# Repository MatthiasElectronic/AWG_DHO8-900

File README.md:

Artificial Waveform Generator for DHO800 and DHO900 series
===

This is a daughter board for the Rigol DHO800 or DHO900 series oscilloscopes to add the missing hardware for the function generator.  
State: finished and working

[Download all files as zip archive here](https://github.com/MatthiasElectronic/AWG_DHO8-900/archive/refs/heads/main.zip)

Discussion thread: https://www.eevblog.com/forum/testgear/awg-function-generator-for-dho800-900-series-oscilloscopes/

Hands-On video by Thomas from "hochohmig": https://www.youtube.com/watch?v=W03NUFdP6oc

Table of Contents
===
1. [Target of this project](#target-of-this-project)
2. [Versions](#versions)
3. [Performance](#performance)
4. [Requirements](#requirements)
5. [Cost and Ordering](#cost-and-ordering)
6. [Interface between Mainboard and AWG daughter board](#interface-between-mainboard-and-awg-daughter-board)
7. [Topology discussion and design decisions](#topology-discussion-and-design-decisions)
8. [Possible Improvements](#possible-improvements)
9. [Thanksgiving](#thanksgiving)
10. [Disclaimer](#disclaimer)

Target of this project
-------
1. This is NOT a copy of the original function generator, but it uses the same interface and same DAC.
2. This design is optimized for cheap production including assembly, by the minimizing the amount of "extended components" from the JLCPCB manufacturer.
3. Minimizing distortion (THD) and noise (SNR) is achieved.
4. The ADC output filter is designed for better pulse and step response, therby having worse anti-alias attenuation (for >10MHz signals) and slight passband signal attenuation
5. Gain and offset tolerances are worse. A significant contributor is anyhow on the oscilloscope mainboard, so perfection cannot be achieved. However, if unlucky, tolerances in this project can mathematically hit quite hard.
6. As the original AWG, this function generator is designed for a 50 OHm coax cable with high impedance termination.

Versions
-------
V1: Original version, not recommended due to an offset bug and smaller mechanical misalignments.  
V2: Second version, not recommended due to a bug with OPA2673 sometimes getting hot. The fix with V3 is to connected Pins A0 and A1 to GND instead of -6.5V.  
V3: Recommended version.  
More details are in the history page in the schematic.

Performance
---
All signals are created with this AWG board, mounted on a DHO804 with a DHO924S vendor.bin.  
Measured on V1 PCB with the modifications of the V2 schematic.  

### Switching edges of a rectangular waveform
The switching edges are clean. trise & tfall are 15.5ns. This is a picture of maximum amplitude (+/-5V), but rise and fall times were measured identical for smaller voltages.  

### Bandwidth
The -3dB point is slightly above 25MHz. At the maximum selectable frequency of 25MHz, a peak-to-peak voltage of 719mV is measured, which is just above the 707mV of the -3dB point.  

### Distortion / THD
Distortion is over the most parts independent from the amplitude, just at very small amplitudes this is different.  
Here, a measurement of a 1kHz sine signal at 10V and 100mV peak-to-peak voltage is provided.  
At 10Vpp, the dominant HD3 is at ca. -62dB, so THD should be below -60dB.  

### Noise / SNR
**Noise measurement setup:**  
A sine signal at very low frequency is applied, the trigger is set to the crossover and the horizontal range is small such that the signal appears as DC.  
→ This way, AC RMS can be measured and equals the RMS noise at that signal amplitude. However, ultra low frequency noise is not visible.

**Noise at 2Vpp signal amplitude:**  
  
Noise RMS = 334µV, Signal RMS = 707mV => SNR = 67dB

**Noise at 10Vpp signal amplitude:**  
  
Noise RMS = 5.2mV, Signal RMS = 3.54V => SNR = 57dB

**Noise source**  
The measured noise levels are dominated by ripples/spikes from radiated EMI of the switching requlators on the mainboard with unshielded inductors.  
A 1.3MHz ripple is always present.  
A 740kHz ripple is only visible for >2Vpp, when the x10 gain stage (relay K4) is active..  
In the following FFT of a 10Vpp 1MHz sine signal, both ripples appear as peaks:  
  
Luckily, this is coupled into the circuit before the attenuators, so at smaller signal amplitudes also the EMI ripple is attenuated.

In addition, there are random (burst mode) spikes clearling coming from the PSU brick. They can even be measured with the AWG switched off.  

**To clarify: The noise/ripple is small enough, it is not visible in time domain unless having a very small amplitude.**

### Gain and Offset accuracy
My prototype has -3mV DC offset, coming directly from the motherboard on the target "DC offset" pin. This is the most noticable offset error, because this one is fully visible at the smallest signal amplitudes.  
Fixed this for my board, but this is completely related to tolerance. Additional offset errors are given in dependency of the AC gain and range selection, also this is amplified by 10 when the output signal exceeds 1Vp.  

My oscilloscope mainboard has a gain error of 3% between highest and lowest gain reference value. This is the most dominant part of the gain error, so if there is a need to fix this tolerance, this has to be done specific for each oscilloscope.

Requirements
--------
**Change vendor.bin**  
To add this AWG to the oscilloscope, a modified vendor.bin (DHO914S or DHO924S) to enable the AWG software functionalities is required.
https://www.eevblog.com/forum/testgear/hacking-the-rigol-dho800900-scope/msg5344076/#msg5344076

**Offset Removal**  
After modifying the vendor.bin, a DC offset in the analog measurement channels is there and might even not be removable by recalibration.  
A firmware update AFTER changing the vendor.bin, followed by a recalibration helps. I assume that the FPGA fimware is changed during a firmware update in dependency of the vendor.bin.

**Hardware version resistors**  
Update: There is no need to change the resistors for version detection - both DHO800 and DHO900 series oscilloscopes work without changing resistors.

**Add missing components to the mainboard**  
The DHO800 series oscilloscopes are missing some parts on the mainboard.  
- The connectors (1.27mm female sockets) 2x20 and 2x5 have to be added (this might be helpful, thanks to Mechatrommer: https://www.youtube.com/watch?v=dBg6KQtSWTM)
- Two OP Amps (3PEAK TP1282L1-VR) have to be added for the offset and gain analog values. These are not really suited for this operation (because they are not officially input rail-rail), but somehow this still works and they are also placed on the original DHO900 series.
- The BNC connector is missing, but as this part is extremely high and nowhere to find, I instead increased the AWG PCB size and simply mounted a smaller BNC connector on the AWG board. So no extra BNC connector on the mainboard. When soldering the BNC connector onto the daughterboard, I suggest to do this as the last step. The SMD PCB interconnects have some tolerance and also the BNC connector ideally should not be pushed completely into the PCB to achieve the same height as the "trigger out" from the mainboard. I aligned the connector before soldering with the AWG daughterboard mounted on the mainboard.
- The board needs to be fixed to the mounting holes. M4 screws with two M4 fasteners were sufficient, but are slightly too large (soldermask IS the isolation...). A better solution (idea from hochohmig.de) are solderable M3 through hole taps, this is cleaner and does not require access to the backside of the mainboard. Securing the daughterboard to the mainboard with the mounting holes is absolutely necessary, the PCB interconnects alone are not sufficient as the BNC connector is not fastened to the case.
- A hole needs to be drilled in the plastic casing for the BNC connector.  

Luckily, all remaining components (resistors, reference voltages, digital interface, …) are already assembled.

**It is NOT necessary to add any additional RAM to the DHO800 series.**

Cost and Ordering
-------
Total cost for 1 board should be ca. 50€.

All components (apart from the connectors) are soldered on the top layer. The PCB is a four layer board.  
This allowed economic assembly with JLCPCB (not sponsored), which is very cheap when using the preferred components. So the whole design is optimized around these preferred components to keep cost low. However, there are some components that are extended (and this costs ca. 3€ each extra). So most of them were ordered on LCSC, because this order was anyways necessary for the connectors and the OP-Amps on the main board.
All parts in this design files have a LCSC number, which makes ordering at LCSC or JLCPCB very simple.
Just be sure that you
1. Have a hot air station or let the QFN packages be soldered (DAC & OP-Amp). Even when ignoring the bottom central GND-pad, this won’t be easy with a simple soldering iron.
2. Use a four layer bord with the recommended or a similar stackup as documented on the first page of the schematic to have somewhat correct impedances.
3. Have accessable vias such that you can use them as measurement points if something does not work.
4. Do not choose a different inductor with a larger height for the step down converters, as there is no space to the casing.

When keeping extended components low (I only chose the SMD inductor), then this can be quite cheap. I ended up with 34€ on JLCPCB for 5 partly assembled boards and 41€ on LCSC for components for 2 boards, including tax and shipment. This adds up to 75€. It should be ca. 53€ if I only ordered components for 1 board. (05/2025)

Interface between Mainboard and AWG daughter board
----
CLK = Sample rate = 156MHz  
The digital data is ALWAYS completely using up the headroom of the DAC.  
Adjustments on the gain are only done by the analog gain input voltage, not digitally.  
With Amplitude = Vpp set to 2V, all attenuation/amplification stages K1-K4 are disabled and the analog gain input is at its maximum value.  
Still unclear is the "Protection" output signal, also it seems strange that this has to be pulled down to negative voltage.  
The 5 relays are: /sqrt(10), /10, /10, *10, On/Off

Topology discussion and design decisions
---
The topolology is  

The DAC itself is the same as on the original AWG board, but in a much cheaper QFN package. The allowed DAC output current was significantly overdriven in the original design, thus I reduced this current.

The OP amps are completely exchanged in favor for the price. The original 1GHz part just seemed to be overkill for a 50MHz signal generator. I chose the 230MHz OPA2673 instead. Sadly, there is nothing cheap in between that has high voltage and high bandwith. But the slew rate is sufficient.

Power rails are reduced to only +6.5V and -6.5V, which is just sufficient for the maximum +5V / -5V signal output voltage and at the border of the allowed OP amp operating conditions. These are both switchers, ripple is kept low by having forced PWM and filtering directly at the OP amp inputs. There is no need for LDOs as most LDOs cannot remove the 1.1MHz ripple. The 5V relays are rated for this voltage, so this is great as well.
Although the original board had +15V/-12V, the same maximum output signal is achieved. Having only 6.5V means that the DC offset stage had to be redone, therefore all PI attenuators and OP amp gains had to be changed. As an easy addon, I also added matched impedances on the PCB.

The DAC output filter is completly redone. The original filter required very specific and uncommon component values, which are nowhere availlable, so this had to be completely changed.

In the original design there was a 9th oder elliptic filter, which sounds great for HF suppression, but has a terrible step response. As I wanted solid edges for rectangular signals, I opted for a filter with a much better phase. While also optimizing for minimum component variation, this turned out to be a bit „creative“ and a 5th order lowpass filter (somewhere in between butterworth and bessel). Simulation in Spice looked promising, but the measured edges (see above, trise/fall = 15.5ns) are slightly slower than simulated (10ns).

As can be seen below, the step response is much better while not exceeding the OP ampl slew rate. Looking at the attenuation over frequency, obviously the elliptic filter is better. My filter has a slight attenuation in the upper passband and a not so perfect attenuation at the sample frequency (156MHz).

Attenuation in the passband: This is noticable for frequencies above 10MHz, but can be corrected for sine signals by manually adjusting the amplitude.

Aliasing: Aliasing can only occur above the Nyquist frequency (78MHz). For signals with lower frequencies (e. g. <1MHz), where fsig << fsample, this is not important as the sinc-behavior in the frequency domain of the sample and hold circuit does sufficently suppress any aliasing (sinc(1-1MHz/156MHz)=-44dB), in addition to the lowpass attenuation. For larger frequencies, this will be worse and probably noticable in the FFT or a spectrum viewer.

Conclusion:  
→ a worse aliasing attenuation, relevant only at high frequencies
→ a better behavior in the step and impulse response

Possible Improvements
---
...which I am not going to solve, but feel free to contribute.  
- the M4 fasteners are too large, more space is required as the solder mask is currently the only line of defence.  
- a DC offset potentiometer would be helpful  
- improve the gain accuracy, but this can get very difficult  
- choose connectors with through-hole alignment pins for easier assembly, but this might require better measurement of the dimensions.
- Eliminate the magnetic EMI incoupling of the switching regulators on the mainboard. Easiest solution could be swapping layer 3 (GND) and layer 4 (signal) and correcting trace widths for the impedances.
  However, as this is magnetic near field, this might not be sufficent. I tried some aluminum kitchen foil connected to GND as a shield, which brought -3dB. A floating thin iron sheet brought -10dB.
  Another option could be to replace the unshielded inductors on the main board with shielded ones.

Be warned that on the left hand side from the relays, the plastic case gets very close to the PCB, so even large MLCCs or SMD inductors can be too large and the relays definitly are.

Thanksgiving
---
Thanks to  
Everybody contributing to the [Hacking the Rigol DHO800/900 Scope](https://www.eevblog.com/forum/testgear/hacking-the-rigol-dho800900-scope/) thread  
Pu6k1n [EEVBlog] for the [schematic of the reverse-engineered original AWG](https://www.eevblog.com/forum/testgear/hacking-the-rigol-dho800900-scope/?action=dlattach;attach=2492911), the pinning helped a lot  
AndyBig [EEVBlog] for all information about DHO800 to DHO900 vendor.bin modification and reporting a bug with V2  
Mechatrommer [EEVBlog] for inspiration from his own AWG attempt and lots of tiny information  
Thomas from [hochohmig.de](https://www.hochohmig.de/) for providing calculation tools, testing the board and creating a [demonstration video - check out his channel](https://www.youtube.com/watch?v=W03NUFdP6oc&t=1s)  
Contributers to KiCad and the library plugins

Disclaimer
---
This is published with CERN-OHL-W-2.0 license, which is accessible in license.txt.
No liability is provided for this not working or causing any form of damage or harm. This is not a product, but a development board. Use at your own risk.  
This project is influenced by the original AWG from Rigol, so only recommended for personal use. Although not checked, selling this AWG could possibly violate patents or rights of Rigol.

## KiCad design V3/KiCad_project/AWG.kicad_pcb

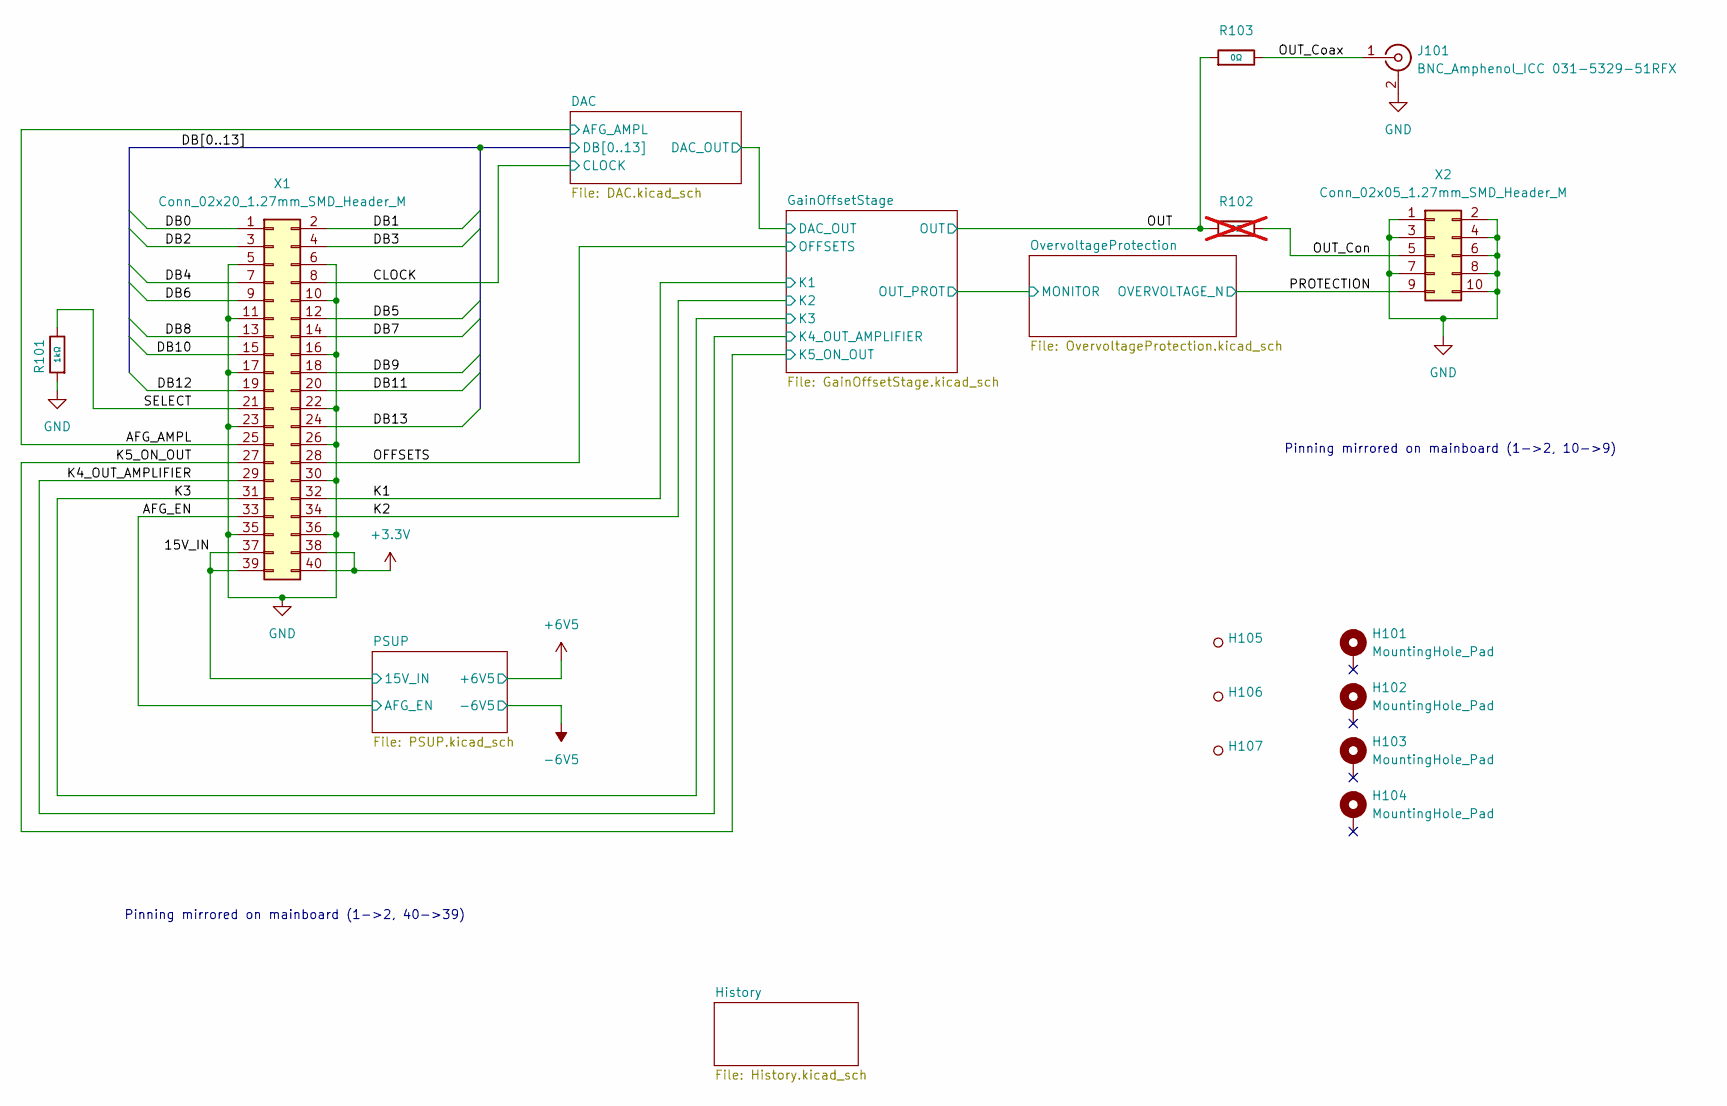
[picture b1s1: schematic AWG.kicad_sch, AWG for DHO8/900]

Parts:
H101, H102, H103, H104: MountingHole_Pad; MountingHole_4.0mm_SmallPad
H105, H106, H107: Hole_Tooling_JLCPCB
J101: BNC_Amphenol_ICC 031-5329-51RFX; LCSC C5443992
R101: 1kΩ; R_0603; Overload Voltage (Max) 75V; Tolerance ±1%; Part 0603WAF1001T5E; LCSC C21190
R102: 0Ω; R_0603; Overload Voltage (Max) 75V; Tolerance ±1%; Part 0603WAF0000T5E; LCSC C21189; not fitted
R103: 0Ω; R_0603; Overload Voltage (Max) 75V; Tolerance ±1%; Part 0603WAF0000T5E; LCSC C21189
X1: Conn_02x20_1.27mm_SMD_Header_M; PinHeader_2x20_P1.27mm_Vertical_SMD; LCSC C2881925
X2: Conn_02x05_1.27mm_SMD_Header_M; PinHeader_2x05_P1.27mm_Vertical_SMD; LCSC C2881910

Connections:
+3.3V: X1.38, X1.40; also elsewhere on the board
/15V_IN: X1.37, X1.39; also elsewhere on the board
/AFG_AMPL: X1.25; also elsewhere on the board
/AFG_EN: X1.33; also elsewhere on the board
/CLOCK: X1.8; also elsewhere on the board
/DB0: X1.1; also elsewhere on the board
/DB1: X1.2; also elsewhere on the board
/DB2: X1.3; also elsewhere on the board
/DB3: X1.4; also elsewhere on the board
/DB4: X1.7; also elsewhere on the board
/DB5: X1.12; also elsewhere on the board
/DB6: X1.9; also elsewhere on the board
/DB7: X1.14; also elsewhere on the board
/DB8: X1.13; also elsewhere on the board
/DB9: X1.18; also elsewhere on the board
/DB10: X1.15; also elsewhere on the board
/DB11: X1.20; also elsewhere on the board
/DB12: X1.19; also elsewhere on the board
/DB13: X1.24; also elsewhere on the board
/K1: X1.32; also elsewhere on the board
/K2: X1.34; also elsewhere on the board
/K3: X1.31; also elsewhere on the board
/K4_OUT_AMPLIFIER: X1.29; also elsewhere on the board
/K5_ON_OUT: X1.27; also elsewhere on the board
/OFFSETS: X1.28; also elsewhere on the board
/OUT: R102.1, R103.1; also elsewhere on the board
/OUT_Coax: J101.1 (In), R103.2
/OUT_Con: R102.2, X2.5
/PROTECTION: X2.9; also elsewhere on the board
/SELECT: R101.2, X1.21
GND: J101.2 (Ext), R101.1, X1.5, X1.6, X1.10, X1.11, X1.16, X1.17, X1.22, X1.23, X1.26, X1.30, X1.35, X1.36, X2.1, X2.2, X2.3, X2.4, X2.6, X2.7, X2.8, X2.10; also elsewhere on the board

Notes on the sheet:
Pinning mirrored on mainboard (1->2, 40->39)
Pinning mirrored on mainboard (1->2, 10->9)

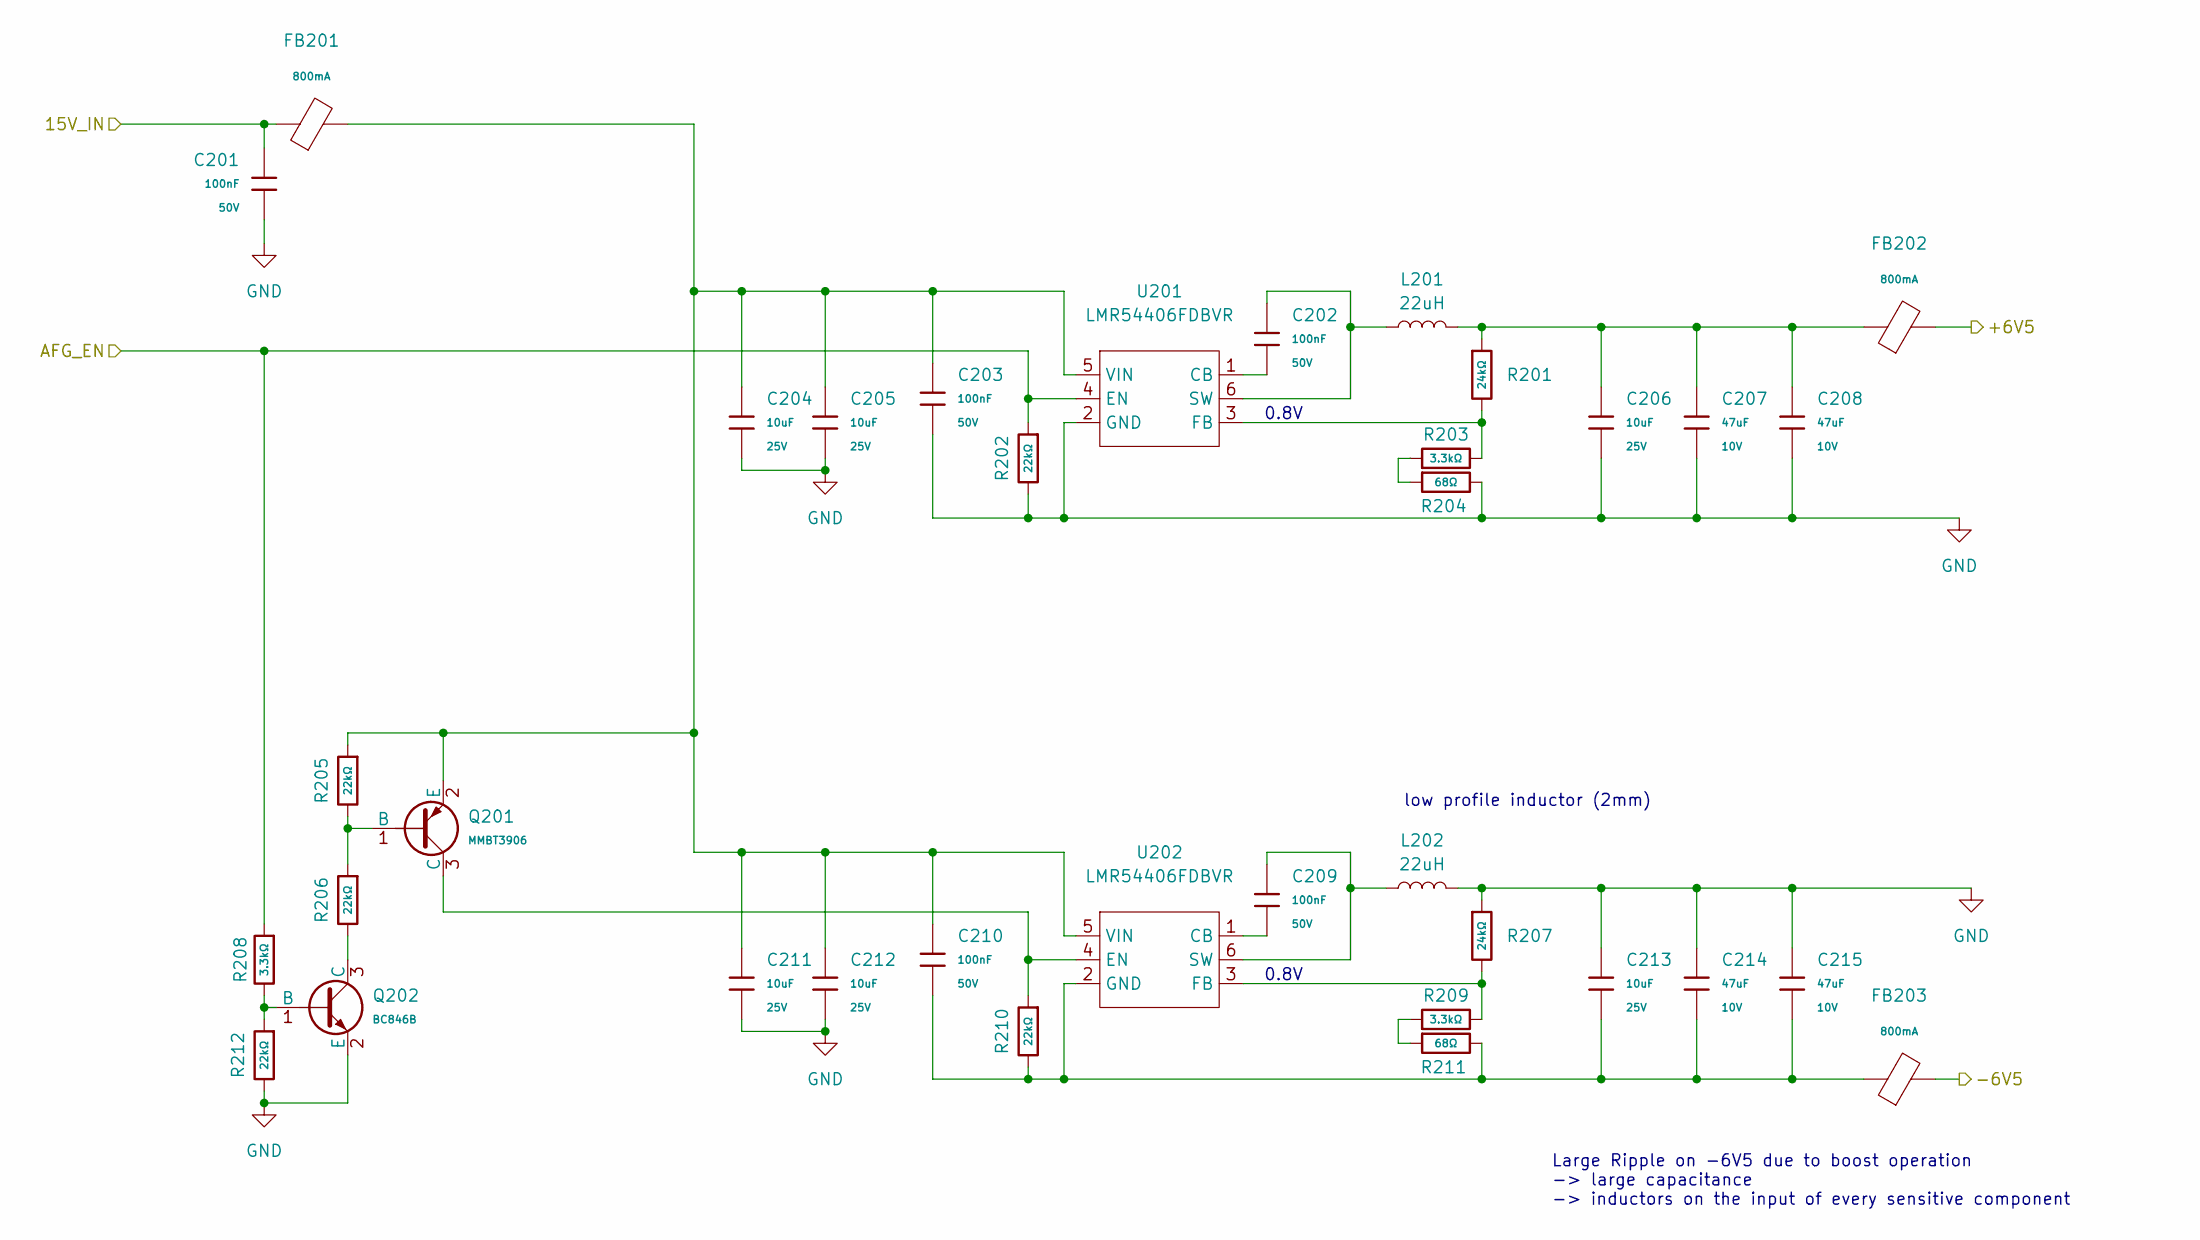
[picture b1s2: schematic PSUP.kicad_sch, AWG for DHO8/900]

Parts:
C201, C202, C203, C209, C210: 100nF; C_0603; Voltage Rated 50V; Tolerance ±10%; Part CC0603KRX7R9BB104; LCSC C14663
C204, C205, C206, C211, C212, C213: 10uF; C_0805; Voltage Rated 25V; Tolerance ±10%; Part CL21A106KAYNNNE; LCSC C15850
C207, C208, C214, C215: 47uF; C_1206; Voltage Rated 10V; Tolerance ±20%; Part CL31A476MPHNNNE; LCSC C96123
FB201, FB202, FB203: FB_0805; Current Rating 800mA; Tolerance ±25%; Part GZ2012D101TF; LCSC C1015
L201, L202: 22uH; L_APV_ANR5045; LCSC C440232
Q201: MMBT3906; Q_SOT-23; Part MMBT3906; LCSC C7420354
Q202: BC846B; Q_SOT-23; Part BC846B; LCSC C20069134
R201, R207: 24kΩ; R_0603; Overload Voltage (Max) 75V; Tolerance ±1%; Part 0603WAF2402T5E; LCSC C23352
R202, R205, R206, R210, R212: 22kΩ; R_0603; Overload Voltage (Max) 75V; Tolerance ±1%; Part 0603WAF2202T5E; LCSC C31850
R203, R208, R209: 3.3kΩ; R_0603; Overload Voltage (Max) 75V; Tolerance ±1%; Part 0603WAF3301T5E; LCSC C22978
R204, R211: 68Ω; R_0603; Overload Voltage (Max) 75V; Tolerance ±1%; Part 0603WAF680JT5E; LCSC C27592
U201, U202: LMR54406FDBVR; SOT-23-6; Manufacturer Part LMR54406FDBVR; LCSC C3193129

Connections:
+6V5: FB202.2; also elsewhere on the board
-6V5: FB203.2; also elsewhere on the board
/15V_IN: C201.1, FB201.1; also elsewhere on the board
/AFG_EN: R202.1, R208.1, U201.4 (EN); also elsewhere on the board
GND: C201.2, C203.2, C204.2, C205.2, C206.2, C207.2, C208.2, C211.2, C212.2, C213.1, C214.1, C215.1, L202.2, Q202.2 (E), R202.2, R204.2, R207.1, R212.2, U201.2 (GND); also elsewhere on the board
unnamed: C206.1, C207.1, C208.1, FB202.1, L201.2, R201.1
unnamed: Q201.1 (B), R205.2, R206.1
unnamed: Q201.3 (C), R210.1, U202.4 (EN)
unnamed: C203.1, C204.1, C205.1, C210.1, C211.1, C212.1, FB201.2, Q201.2 (E), R205.1, U201.5 (VIN), U202.5 (VIN)
unnamed: Q202.1 (B), R208.2, R212.1
unnamed: Q202.3 (C), R206.2
unnamed: R203.1, R204.1
unnamed: R209.1, R211.1
unnamed: C202.2, U201.1 (CB)
unnamed: R201.2, R203.2, U201.3 (FB)
unnamed: C202.1, L201.1, U201.6 (SW)
unnamed: C209.2, U202.1 (CB)
unnamed: R207.2, R209.2, U202.3 (FB)
unnamed: C210.2, C213.2, C214.2, C215.2, FB203.1, R210.2, R211.2, U202.2 (GND)
unnamed: C209.1, L202.1, U202.6 (SW)

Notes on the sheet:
0.8V
Large Ripple on -6V5 due to boost operation -> large capacitance -> inductors on the input of every sensitive component
low profile inductor (2mm)

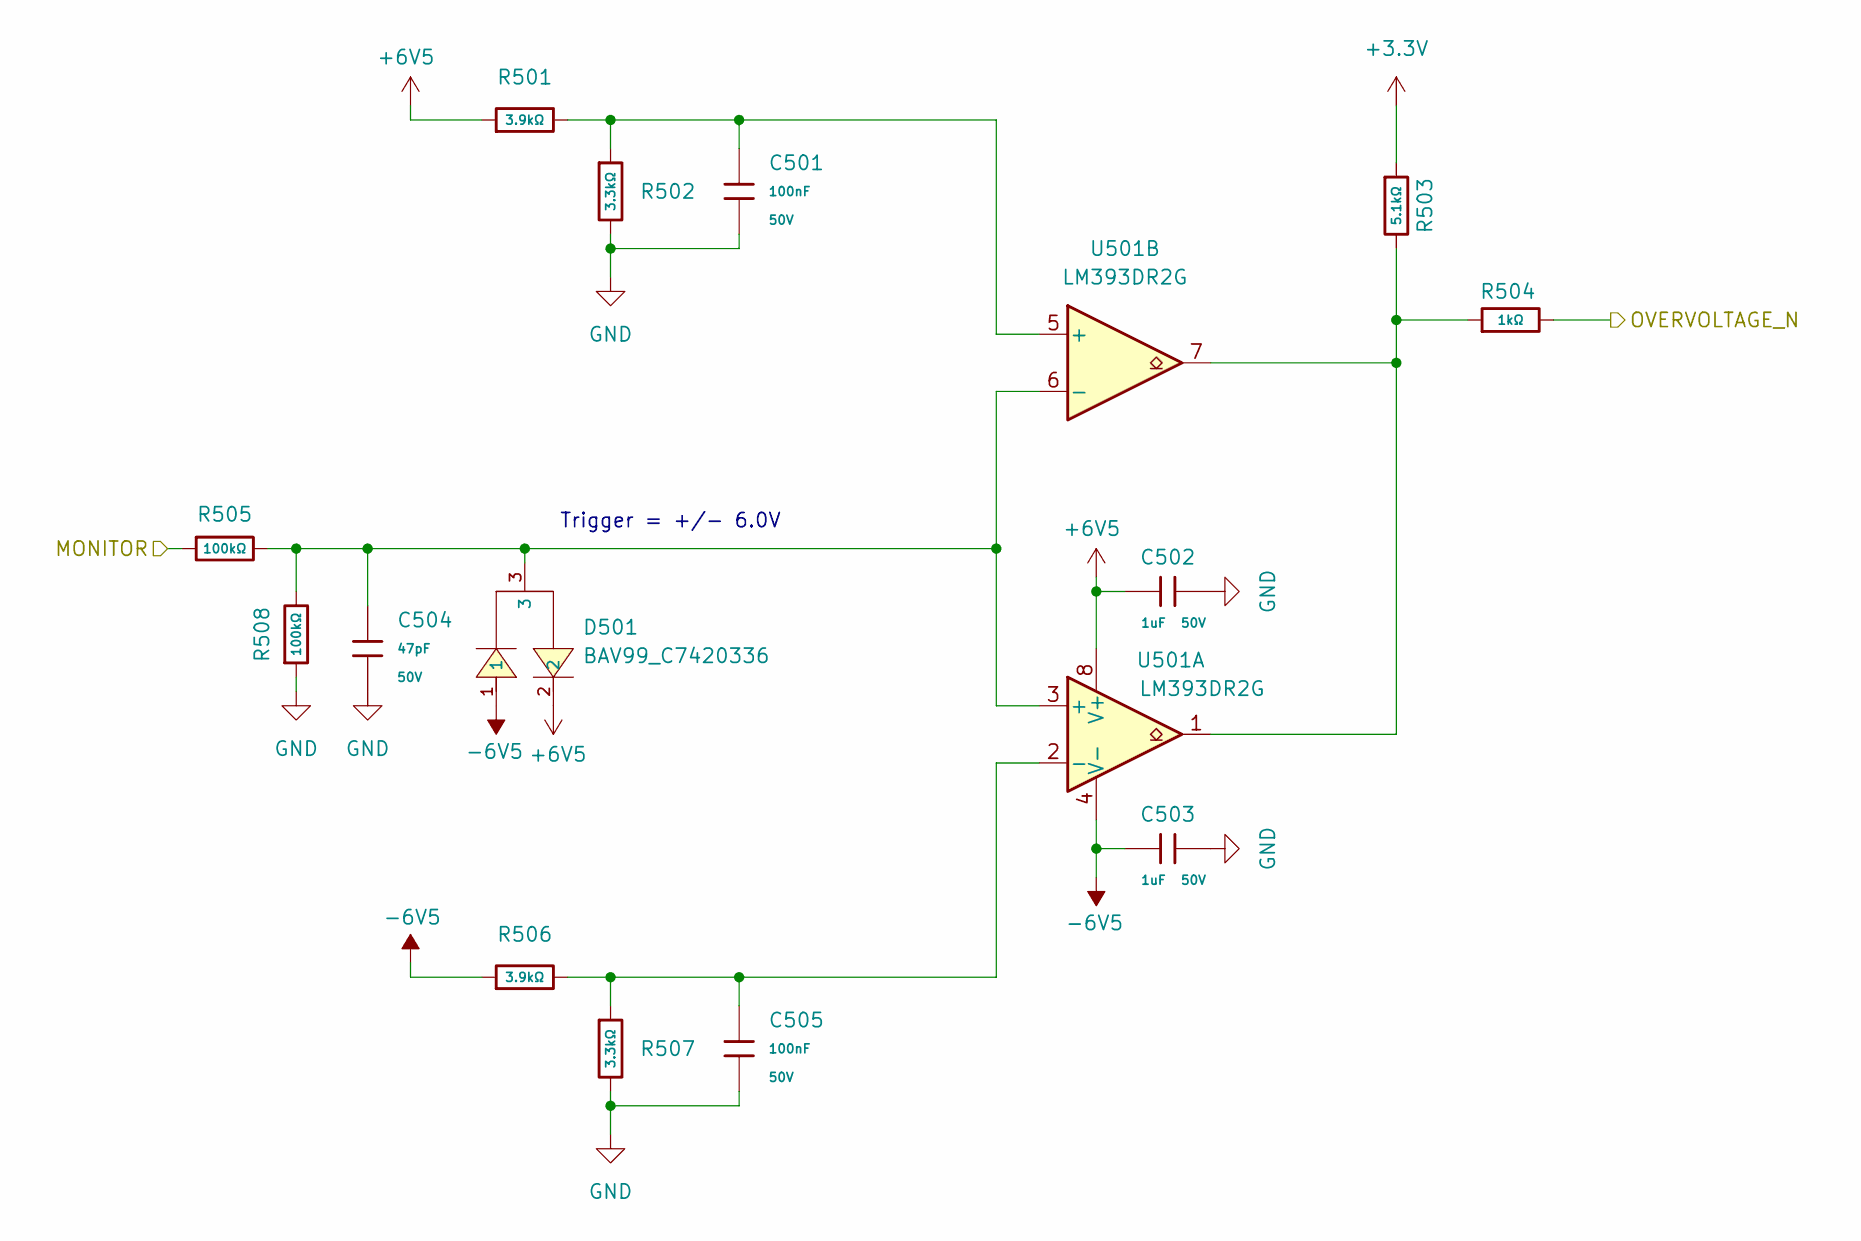
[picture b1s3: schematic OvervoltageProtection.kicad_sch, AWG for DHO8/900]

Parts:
C501, C505: 100nF; C_0603; Voltage Rated 50V; Tolerance ±10%; Part CC0603KRX7R9BB104; LCSC C14663
C502, C503: 1uF; C_0603; Voltage Rated 50V; Tolerance ±10%; Part CL10A105KB8NNNC; LCSC C15849
C504: 47pF; C_0603; Voltage Rated 50V; Tolerance ±5%; Part CL10C470JB8NNNC; LCSC C1671
D501: BAV99_C7420336; SOT-23-3_L2.9-W1.3-P1.90-LS2.4-BR; Reverse Voltage (Vr) 100V; Forward Voltage (Vf@If) 1.25V@150mA; Part BAV99; LCSC C7420336
R501, R506: 3.9kΩ; R_0603; Overload Voltage (Max) 75V; Tolerance ±1%; Part 0603WAF3901T5E; LCSC C23018
R502, R507: 3.3kΩ; R_0603; Overload Voltage (Max) 75V; Tolerance ±1%; Part 0603WAF3301T5E; LCSC C22978
R503: 5.1kΩ; R_0603; Overload Voltage (Max) 75V; Tolerance ±1%; Part 0603WAF5101T5E; LCSC C23186
R504: 1kΩ; R_0603; Overload Voltage (Max) 75V; Tolerance ±1%; Part 0603WAF1001T5E; LCSC C21190
R505, R508: 100kΩ; R_0603; Overload Voltage (Max) 75V; Tolerance ±1%; Part 0603WAF1003T5E; LCSC C25803
U501: LM393DR2G; SOIC-8_3.9x4.9mm_P1.27mm; LCSC C7955

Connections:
+3.3V: R503.1; also elsewhere on the board
+6V5: C502.1, D501.2, R501.1, U501.8 (V+); also elsewhere on the board
-6V5: C503.1, D501.1, R506.1, U501.4 (V-); also elsewhere on the board
/GainOffsetStage/OUT_PROT: R505.1; also elsewhere on the board
/PROTECTION: R504.2; also elsewhere on the board
GND: C501.2, C502.2, C503.2, C504.2, C505.2, R502.2, R507.2, R508.1; also elsewhere on the board
unnamed: R503.2, R504.1, U501.1, U501.7
unnamed: C504.1, D501.3, R505.2, R508.2, U501.3 (+), U501.6 (-)
unnamed: C505.1, R506.2, R507.1, U501.2 (-)
unnamed: C501.1, R501.2, R502.1, U501.5 (+)

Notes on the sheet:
Trigger = +/- 6.0V

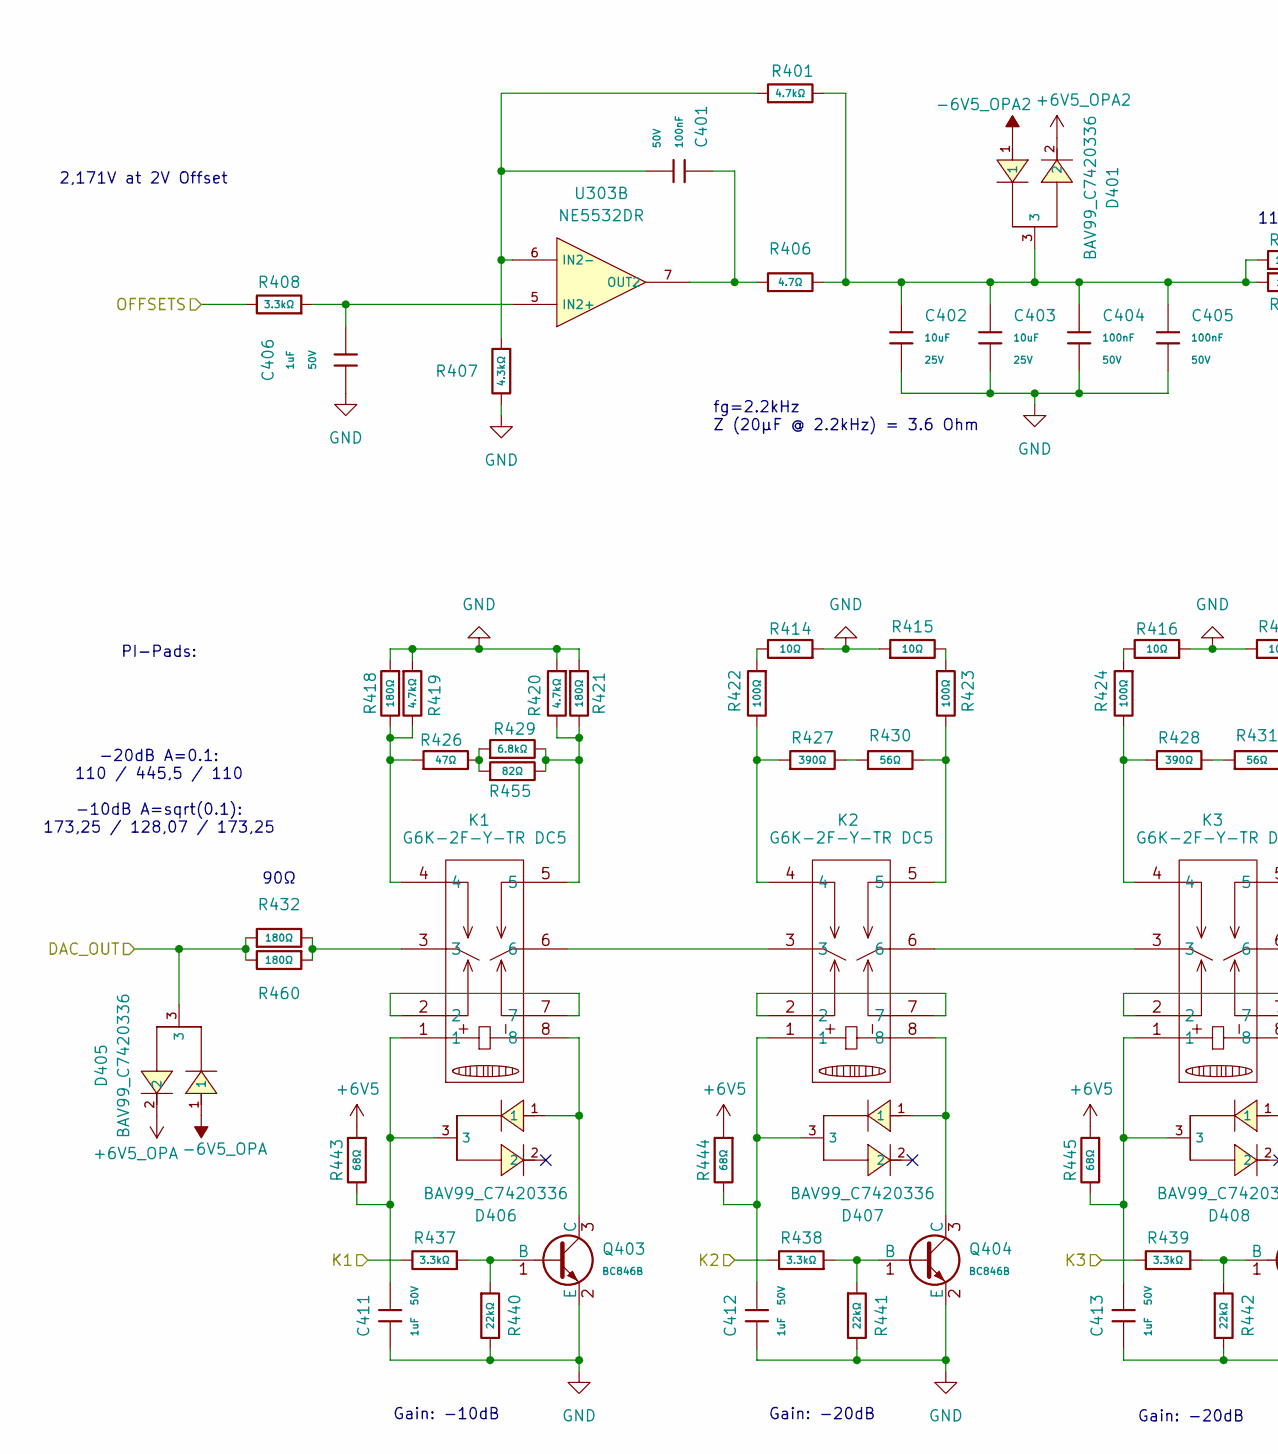
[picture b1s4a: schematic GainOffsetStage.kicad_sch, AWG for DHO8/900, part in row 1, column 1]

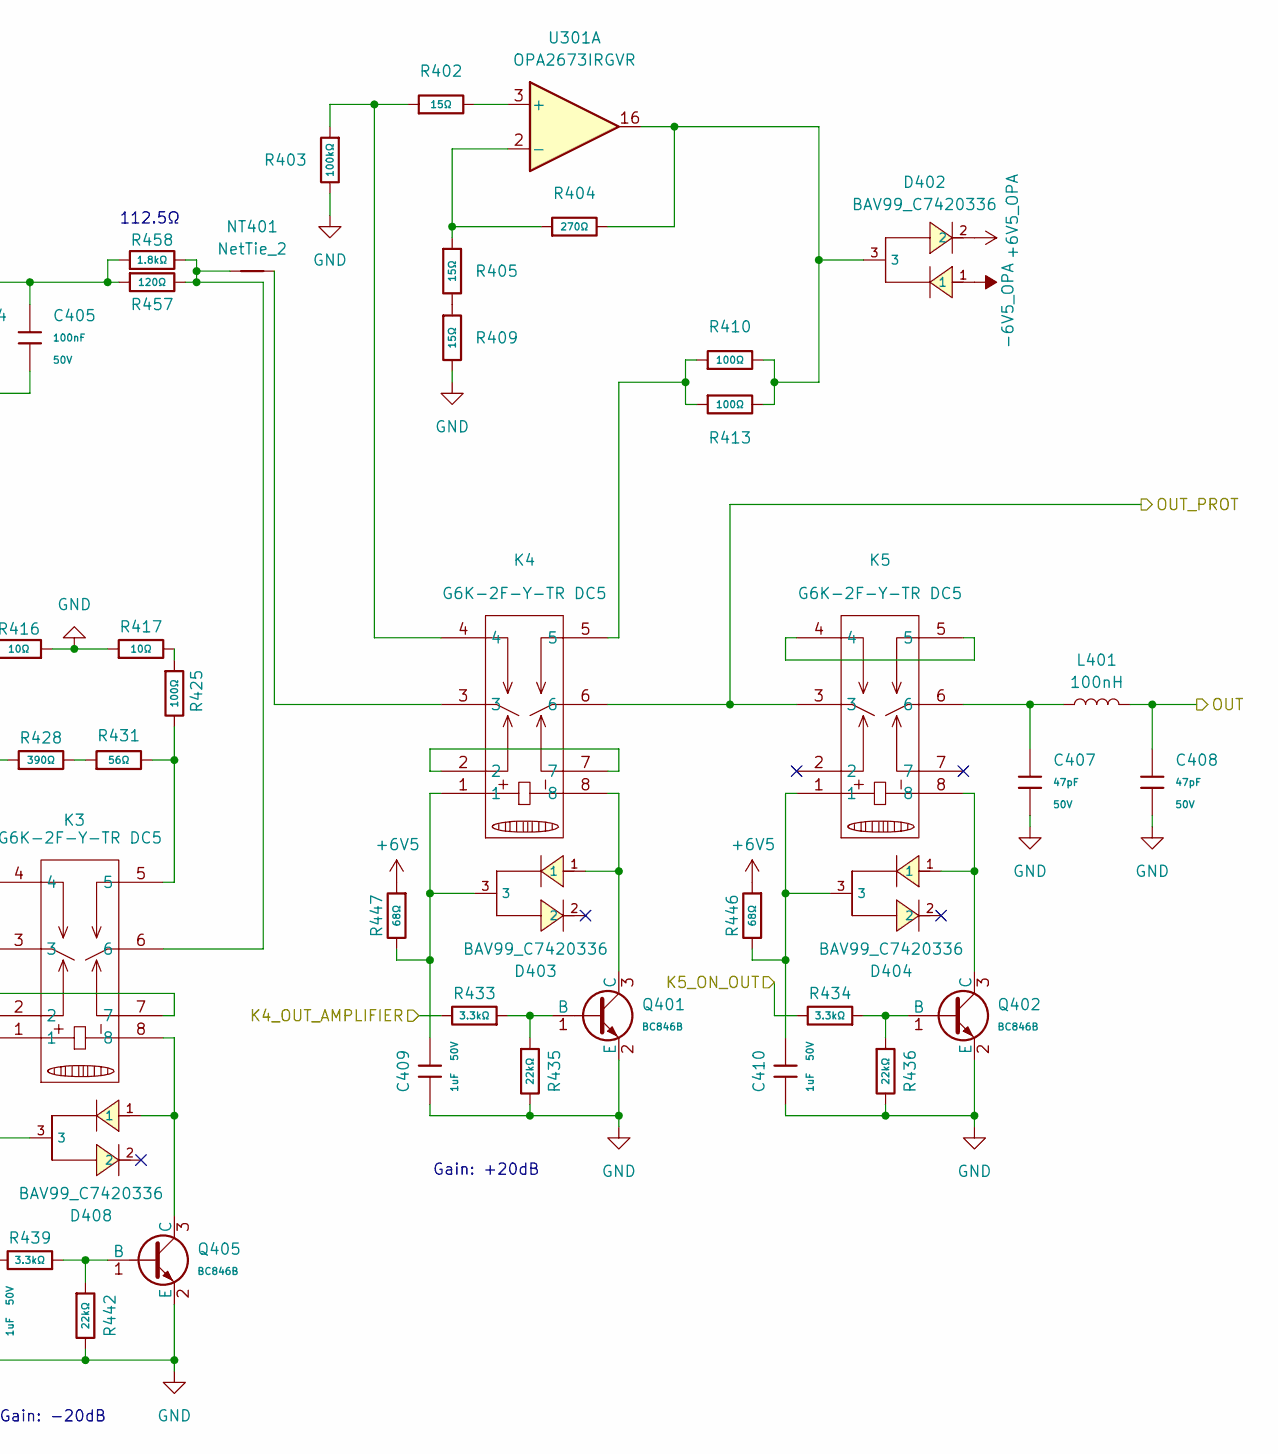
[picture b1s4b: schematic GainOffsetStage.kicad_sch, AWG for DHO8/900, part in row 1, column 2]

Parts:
C401, C404, C405: 100nF; C_0603; Voltage Rated 50V; Tolerance ±10%; Part CC0603KRX7R9BB104; LCSC C14663
C402, C403: 10uF; C_0805; Voltage Rated 25V; Tolerance ±10%; Part CL21A106KAYNNNE; LCSC C15850
C406, C409, C410, C411, C412, C413: 1uF; C_0603; Voltage Rated 50V; Tolerance ±10%; Part CL10A105KB8NNNC; LCSC C15849
C407, C408: 47pF; C_0603; Voltage Rated 50V; Tolerance ±5%; Part CL10C470JB8NNNC; LCSC C1671
D401, D402, D403, D404, D405, D406, D407, D408: BAV99_C7420336; SOT-23-3_L2.9-W1.3-P1.90-LS2.4-BR; Reverse Voltage (Vr) 100V; Forward Voltage (Vf@If) 1.25V@150mA; Part BAV99; LCSC C7420336
K1, K2, K3, K4, K5: RELAY-SMD_G6K-2F-X-XX; Manufacturer Part G6K-2F-Y-TR DC5; LCSC Part Name G6K-2F-Y-TR DC5
L401: 100nH; L_0603; LCSC C98088
NT401: NetTie_2; NetTie-2_SMD_Pad0.5mm
Q401, Q402, Q403, Q404, Q405: BC846B; Q_SOT-23; Part BC846B; LCSC C20069134
R401, R419, R420: 4.7kΩ; R_0603; Overload Voltage (Max) 75V; Tolerance ±1%; Part 0603WAF4701T5E; LCSC C23162
R402, R405, R409: 15Ω; R_0603; Overload Voltage (Max) 75V; Tolerance ±1%; Part 0603WAF150JT5E; LCSC C22810
R403: 100kΩ; R_0603; Overload Voltage (Max) 75V; Tolerance ±1%; Part 0603WAF1003T5E; LCSC C25803
R404: 270Ω; R_0805; Overload Voltage (Max) 150V; Tolerance ±1%; Part 0805W8F2700T5E; LCSC C17590
R406: 4.7Ω; R_0603; Overload Voltage (Max) 75V; Tolerance ±1%; Part 0603WAF470KT5E; LCSC C23164
R407: 4.3kΩ; R_0603; Overload Voltage (Max) 75V; Tolerance ±1%; Part 0603WAF4301T5E; LCSC C23159
R408, R433, R434, R437, R438, R439: 3.3kΩ; R_0603; Overload Voltage (Max) 75V; Tolerance ±1%; Part 0603WAF3301T5E; LCSC C22978
R410, R413: 100Ω; R_1206; Overload Voltage (Max) 200V; Tolerance ±1%; Part 1206W4F1000T5E; LCSC C17901
R414, R415, R416, R417: 10Ω; R_0603; Overload Voltage (Max) 75V; Tolerance ±1%; Part 0603WAF100JT5E; LCSC C22859
R418, R421, R432, R460: 180Ω; R_0603; Overload Voltage (Max) 75V; Tolerance ±1%; Part 0603WAF1800T5E; LCSC C22828
R422, R423, R424, R425: 100Ω; R_0603; Overload Voltage (Max) 75V; Tolerance ±1%; Part 0603WAF1000T5E; LCSC C22775
R426: 47Ω; R_0603; Overload Voltage (Max) 75V; Tolerance ±1%; Part 0603WAF470JT5E; LCSC C23182
R427, R428: 390Ω; R_0603; Overload Voltage (Max) 75V; Tolerance ±1%; Part 0603WAF3900T5E; LCSC C23151
R429: 6.8kΩ; R_0603; Overload Voltage (Max) 75V; Tolerance ±1%; Part 0603WAF6801T5E; LCSC C23212
R430, R431: 56Ω; R_0603; Overload Voltage (Max) 75V; Tolerance ±1%; Part 0603WAF560JT5E; LCSC C25196
R435, R436, R440, R441, R442: 22kΩ; R_0603; Overload Voltage (Max) 75V; Tolerance ±1%; Part 0603WAF2202T5E; LCSC C31850
R443, R444, R445, R446, R447: 68Ω; R_0603; Overload Voltage (Max) 75V; Tolerance ±1%; Part 0603WAF680JT5E; LCSC C27592
R455: 82Ω; R_0603; Overload Voltage (Max) 75V; Tolerance ±1%; Part 0603WAF820JT5E; LCSC C23255
R457: 120Ω; R_1206; Overload Voltage (Max) 200V; Tolerance ±1%; Part 1206W4F1200T5E; LCSC C17909
R458: 1.8kΩ; R_0603; Overload Voltage (Max) 75V; Tolerance ±1%; Part 0603WAF1801T5E; LCSC C4177
U301: OPA2673IRGVR; Texas_RSA_VQFN-16-1EP_4x4mm_P0.65mm_EP2.7x2.7mm; LCSC C1848168
U303: NE5532DR; SOIC-8_L4.9-W3.9-P1.27-LS6.0-BL; Part NE5532DR; LCSC C7426

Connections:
+6V5: R443.1, R444.1, R445.1, R446.1, R447.1; also elsewhere on the board
+6V5_OPA: D402.2, D405.2; also elsewhere on the board
+6V5_OPA2: D401.2; also elsewhere on the board
-6V5_OPA: D402.1, D405.1; also elsewhere on the board
-6V5_OPA2: D401.1; also elsewhere on the board
/DAC/DAC_OUT: D405.3, R432.1, R460.2; also elsewhere on the board
/GainOffsetStage/OUT_PROT: K4.6, K5.3; also elsewhere on the board
/K1: R437.2; also elsewhere on the board
/K2: R438.2; also elsewhere on the board
/K3: R439.2; also elsewhere on the board
/K4_OUT_AMPLIFIER: R433.2; also elsewhere on the board
/K5_ON_OUT: R434.2; also elsewhere on the board
/OFFSETS: R408.2; also elsewhere on the board
/OUT: C408.1, L401.2; also elsewhere on the board
GND: C402.2, C403.2, C404.2, C405.2, C406.1, C407.2, C408.2, C409.1, C410.1, C411.1, C412.1, C413.1, Q401.2 (E), Q402.2 (E), Q403.2 (E), Q404.2 (E), Q405.2 (E), R403.2, R407.2, R409.2, R414.1, R415.1, R416.1, R417.1, R418.1, R419.1, R420.1, R421.1, R435.2, R436.2, R440.2, R441.2, R442.2; also elsewhere on the board
unnamed: C402.1, C403.1, C404.1, C405.1, D401.3, R401.2, R406.2, R457.1, R458.1
unnamed: C407.1, K5.6, L401.1
unnamed: C409.2, D403.3, K4.1, R447.2
unnamed: C410.2, D404.3, K5.1, R446.2
unnamed: C411.2, D406.3, K1.1, R443.2
unnamed: C412.2, D407.3, K2.1, R444.2
unnamed: C413.2, D408.3, K3.1, R445.2
unnamed: D402.3, R404.2, R410.2, R413.2, U301.16
unnamed: K1.2, K1.7
unnamed: K1.3, R432.2, R460.1
unnamed: K1.4, R418.2, R419.2, R426.1
unnamed: K1.5, R420.2, R421.2, R429.2, R455.2
unnamed: K1.6, K2.3
unnamed: K2.2, K2.7
unnamed: K2.4, R422.2, R427.1
unnamed: K2.5, R423.2, R430.2
unnamed: K2.6, K3.3
unnamed: K3.2, K3.7
unnamed: K3.4, R424.2, R428.1
unnamed: K3.5, R425.2, R431.2
unnamed: K3.6, NT401.1, R457.2, R458.2
unnamed: K4.2, K4.7
unnamed: K4.3, NT401.2
unnamed: K4.4, R402.1, R403.1
unnamed: K4.5, R410.1, R413.1
unnamed: K5.4, K5.5
unnamed: Q401.1 (B), R433.1, R435.1
unnamed: D403.1, K4.8, Q401.3 (C)
unnamed: Q402.1 (B), R434.1, R436.1
unnamed: D404.1, K5.8, Q402.3 (C)
unnamed: Q403.1 (B), R437.1, R440.1
unnamed: D406.1, K1.8, Q403.3 (C)
unnamed: Q404.1 (B), R438.1, R441.1
unnamed: D407.1, K2.8, Q404.3 (C)
unnamed: Q405.1 (B), R439.1, R442.1
unnamed: D408.1, K3.8, Q405.3 (C)
unnamed: R405.2, R409.1
unnamed: R414.2, R422.1
unnamed: R415.2, R423.1
unnamed: R416.2, R424.1
unnamed: R417.2, R425.1
unnamed: R426.2, R429.1, R455.1
unnamed: R427.2, R430.1
unnamed: R428.2, R431.1
unnamed: R402.2, U301.3 (+)
unnamed: R404.1, R405.1, U301.2 (-)
unnamed: C406.2, R408.1, U303.5 (IN2+)
unnamed: C401.2, R401.1, R407.1, U303.6 (IN2-)
unnamed: C401.1, R406.1, U303.7 (OUT2)

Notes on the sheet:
PI-Pads:
Gain: +20dB
112.5Ω
Gain: -20dB
2,171V at 2V Offset
fg=2.2kHz Z (20µF @ 2.2kHz) = 3.6 Ohm
90Ω
Gain: -10dB
-20dB A=0.1: 110 / 445,5 / 110 -10dB A=sqrt(0.1): 173,25 / 128,07 / 173,25
